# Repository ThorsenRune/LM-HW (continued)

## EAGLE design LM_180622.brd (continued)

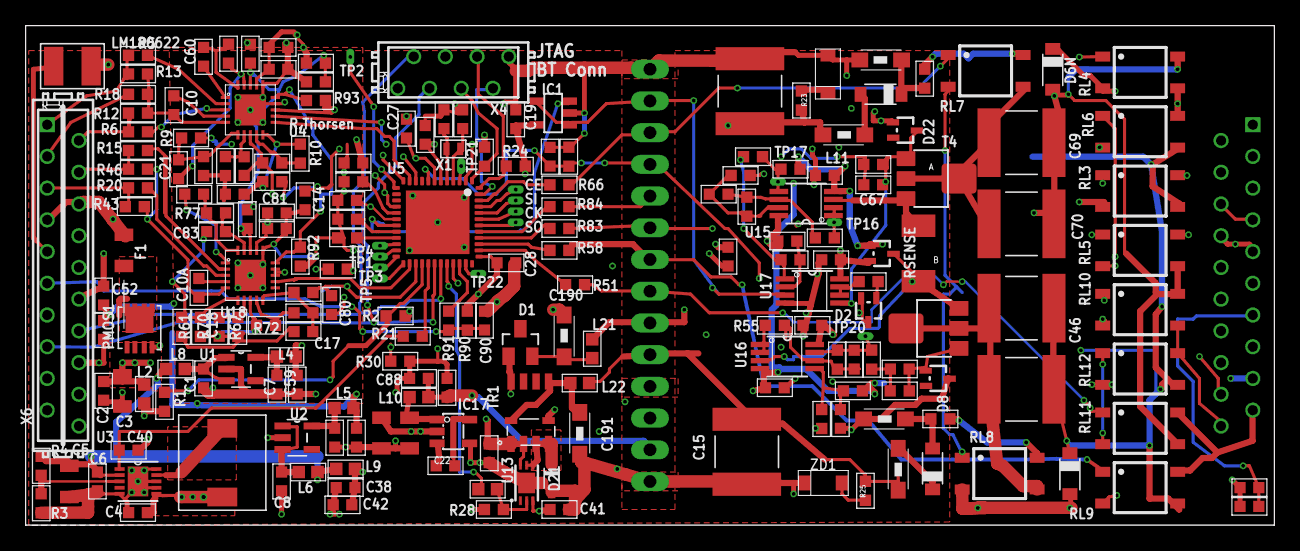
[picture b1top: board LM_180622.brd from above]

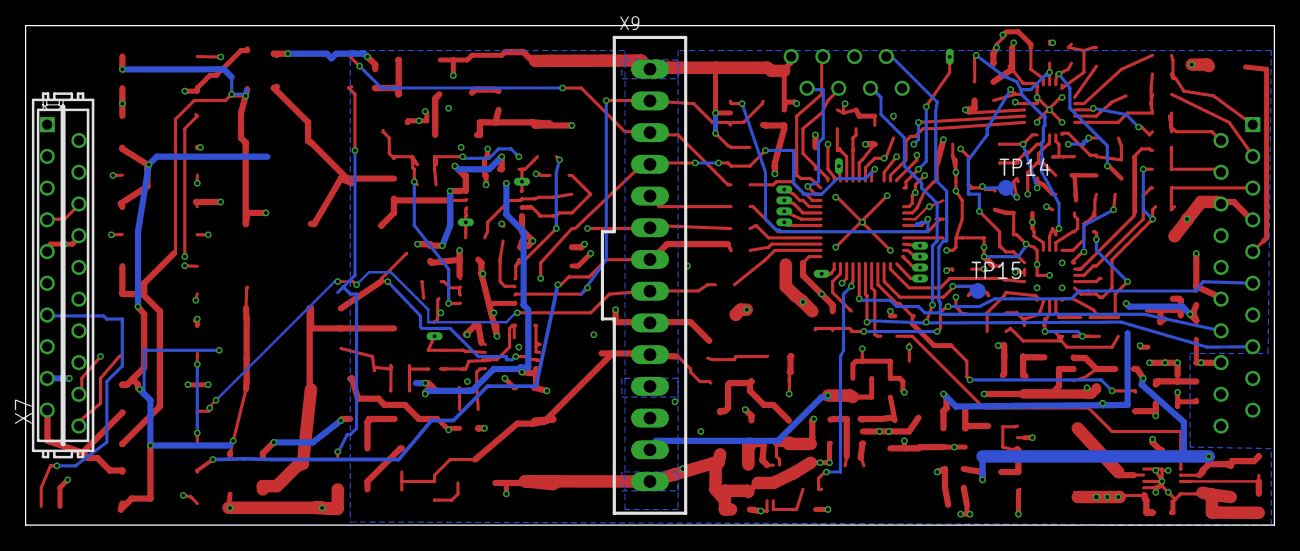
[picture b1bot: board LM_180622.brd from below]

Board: 4 copper layers, 100.0 x 40.0 mm, 216 parts (4 on the bottom side), 149 nets.

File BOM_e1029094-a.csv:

"Reference:,""e1029094-a""";;;;
"Date:,""Fri Jul 20 15:37:21 GMT+200 2018""";;;;
"Generated by:,""Eurocircuits PCBA Visualizer""";;;;

Reference designators;Quantity;MPN;Manufacturer;Description
R30;1;GPR06030R;Generic part;0 Ohms Jumper 0.1W, 1/10W Chip Resistor 0603 (1608 Metric) Moisture Resistant Thick Film
C75, C76;2;C0603C101K5RACTU;Kemet;Capacitor, Ceramic, 100pF 50V 10% X7R
R9, R10, R11, R24, R56, R57, R65, R68, R69, R70, R71, R72;12;GPR0603100K;Generic part;0603, Res 100.0kOhm, 50V, 1.0%, 100mW
C44, C50, C190, C191;4;12062C104KAT2A;AVX;0.1µF ±10% 200V Ceramic Capacitor X7R 1206 (3216 Metric)
C14, C80, C1U15, C1U16, C2U15, C2U16, C19, C20, C23, C24, C28, C31, C40, C41, C42, C45, C48, C49, C53, C67, C82, C86, C88, C90, C144, CU17;26;GPC0603104;Generic part;0603, Cap 100.0nF, 50V, 10.0%, X7R
C55;1;GRM32ER60J107ME20L;Murata;100µF ±20% 6.3V Ceramic Capacitor X5R 1210 (3225 Metric)
R93;1;GPR060310K;Generic part;0603, Res 10.0kOhm, 50V, 1.0%, 100mW
R12, R13, R16, R17, R22, R43, R46, R77, R144, R145;10;CRCW060310M0FKEA;Vishay;10M Ohm ±1% 0.1W, 1/10W Chip Resistor 0603 (1608 Metric) Automotive AEC-Q200 Thick Film
R48, R49;2;GPR060310R;Generic part;0603, Res 10.0Ohm, 50V, 1.0%, 100mW
R7, R8, R21, R61, R67, R89;6;GPR060310K;Generic part;0603, Res 10.0kOhm, 50V, 1.0%, 100mW
C32, C33;2;C0603C100J5GACTU;Kemet;10pF ±5% 50V Ceramic Capacitor C0G, NP0 0603 (1608 Metric)
C1, C2, C4, C6, C7, C8, C9, C16, C29, C30, C38, C52, C54, C58, C59, C81;16;C1608X5R0J106M080AB;TDK;10µF ±20% 6.3V Ceramic Capacitor X5R 0603 (1608 Metric)
R5, R6, R15, R20;4;GPR0603180K;Generic part;0603, Res 180.0kOhm, 50V, 1.0%, 100mW
R28, R40, R42, R62;4;GPR06031M;Generic part;0603, Res 1.0MOhm, 50V, 1.0%, 100mW
R23, R25, R29, R41, R55, R63, R80;7;GPR06031K;Generic part;0603, Res 1.0kOhm, 50V, 1.0%, 100mW
C10, C10A;2;500R14N102JV4T;Johanson Dielectrics Inc.;"1000pF ±5% 50V Ceramic Capacitor C0G, NP0 0603 (1608 Metric) 0.063"" L x 0.032"" W (1.60mm x 0.81mm)"
C22;1;GPC0603105;Generic part;0603, Cap 1uF, 50V, 10.0%, X5R
RSENSE;1;MCPWR10FTEQ2000;Multicomp;RES, THICK FILM, 200R, 1%, 0.75W, 2010
C21, C60, C83, C85;4;C0603C224K3RACTU;Kemet;0.22µF ±10% 25V Ceramic Capacitor X7R 0603 (1608 Metric)
R3;1;GPR0603270K;Generic part;0603, Res 270.0kOhm, 50V, 1.0%, 100mW
R1, R4;2;GPR06032M;Generic part;0603, Res 2.0MOhm, 75V, 1.0%, 100mW
C13, C15, C46, C51, C69, C70;6;C5750X7T2E225K250KE;TDK;2.2µF ±10% 250V Ceramic Capacitor X7T 2220 (5750 Metric)
L2, L3, L4, L5, L6, L8, L9, L10, L21, L22;10;MMZ1608B301CTAH0;TDK;FERRITE BEAD 300 OHM 0603 1LN
C11, C12, C17, C18;4;C0603C333K1RACTU;Kemet;0.033µF ±10% 100V Ceramic Capacitor X7R 0603 (1608 Metric)
R66;1;GPR0603390R;Generic part;0603, Res 390.0Ohm, 50V, 1.0%, 100mW
R2, R90, R91;3;GPR0603390K;Generic part;0603, Res 390.0kOhm, 75V, 1.0%, 100mW
R14, R73;2;GPR06033K3;Generic part;0603, Res 3.3kOhm, 75V, 1.0%, 100mW
C39;1;CGB3B3X5R0J475K055AB;TDK Corporation;"4.7µF ±10% 6.3V Ceramic Capacitor X5R 0603 (1608 Metric) 0.063"" L x 0.032"" W (1.60mm x 0.80mm)"
R19;1;GPR0603470R;Generic part;0603, Res 470.0Ohm, 75V, 1.0%, 100mW
C26, C27, C34;3;GPC0603474;Generic part;0603, Cap 470nF, 50V, 10.0%, X7R
C3, C5;2;GRM219R60J476ME44D;Murata Electronics North America;47µF ±20% 6.3V Ceramic Capacitor X5R 0805 (2012 Metric) GRM Series
L11, L12;2;LQH31MN470K03L;Murata;47µH Unshielded Wirewound Inductor 55mA 10.4 Ohm Max 1206 (3216 Metric)
R18;1;MCWR06X4993FTL;Multicomp;RES, THICK FILM, 499KOHM, 1%, 0.1W, 0603
R64;1;GPR06034K7;Generic part;0603, Res 4.7kOhm, 50V, 1.0%, 100mW
C43, C47;2;GRM21BR60J475KA11L;Murata;4.7µF ±10% 6.3V Ceramic Capacitor X5R 0805 (2012 Metric)
L1;1;B82462G4682M000;EPCOS;6.8µH Shielded Wirewound Inductor 1.65A 50 mOhm Max Nonstandard
R51, R58, R83, R84;4;GPR0603820R;Generic part;0603, Res 820.0Ohm, 50V, 1.0%, 100mW
X1;1;ABS05-32.768KHZ-T;Abracon;32.768kHz ±20ppm Crystal 12.5pF 90 kOhm -40°C ~ 85°C Surface Mount 2-SMD, No Lead
U4, U18;2;AD8232ACPZ-R7;Analog Device;ECG Front End IC Heart Rate Monitoring 20-LFCSP-WQ (4x4)
U15, U16, U17;3;AD8642ARMZ;Analog Device;IC OPAMP JFET 3.5MHZ RRO 8MSOP
U1, U2;2;MIC5255-3.3YM5-TR;Microchip;Linear Voltage Regulator IC Positive Fixed 1 Output 3.3V 150mA SOT-23-5
U5;1;ADUCM360BCPZ128;Analog Device;ARM® Cortex®-M3 ADuCM Microcontroller IC 32-Bit 20 MIPS 128KB (128K x 8) FLASH 48-LFCSP-WQ (7x7)
RL3, RL4, RL5, RL6, RL7, RL8, RL9, RL10, RL11, RL12;10;AQY210S;Panasonic;MOSFET Relay, 350 V, 120 mA, 25 ohm, SPST-NO
TR1;1;ATB322524-0110;TDK;Audio Transformers / Signal Transformers Photoflash Capacitor Charging Transformer
D2, D8, D12, D22;4;BAS40-04W,115;NXP Semiconductors;Diode Array 1 Pair Series Connection Schottky 40V 120mA (DC) Surface Mount SC-70, SOT-323
D1;1;BAV23S,215;Nexperia;Diode Array 1 Pair Series Connection Standard 200V 225mA (DC) Surface Mount TO-236-3, SC-59, SOT-23-3
D6N, D6P, D6P1, D6P2;4;BAV3004W-7-F;Diode Inc;Diode Standard 300V 225mA (DC) Surface Mount SOD-123
F1;1;0805L100WR;Littelfuse;Polymeric PTC Resettable Fuse 6V 1A Ih Surface Mount 0805 (2012 Metric), Concave
ZD1, ZD3;2;KDZLVTFTR150;ROHM Semiconductor;Zener Diode 150V 1W  Surface Mount SOD-123FL
U13;1;LT3484EDCB-1#TRMPBF;Linear Technology/Analog Devices;Photoflash Capacitor Charger PMIC 6-DFN (2x3)
X6;1;9-215464-0;TE Connectivity;"Connector Header Through Hole 20 position 0.100"" (2.54mm)"
X4;1;7-215464-8;TE Connectivity;"Connector Header Through Hole 8 position 0.100"" (2.54mm)"
IC1;1;OPA340NA/3K;Texas Instruments;General Purpose Amplifier 1 Circuit Rail-to-Rail SOT-23-5
PMOS1;1;SIS406DN-T1-GE3;Vishay;N-Channel MOSFET 30V 9A (Ta) 1.5W (Ta) Surface Mount PowerPAK® 1212-8
IC17;1;TPS60400DBVR;Texas Instruments;IC, Unregulated 60mA Charge Pump Voltage Inverter
U3;1;TPS61020DRCRG4;Texas Instrument;DC-DC Switching Boost Step Up Regulator, Adjustable, 900mV-6.5Vin, 1.8V-5.5Vout, 200mAout, SON-10
D21;1;ZHCS400;Diode Inc;Diode Schottky 40V 400mA (DC) Surface Mount SOD-323
T4;1;ZVN4525ZTA;Diode Inc;N-Channel MOSFET 250V 240mA (Ta) 1.2W (Ta) Surface Mount SOT-89-3
T25;1;ZVP4525ZTA;Diodes Incorporated;P-Channel MOSFET 250V 205mA (Ta) 1.2W (Ta) Surface Mount SOT-89-3

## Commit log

2018-12-17 First Version of the LM Hardware
    This hardware is part of a neuroprosthesis aimed at restoring hand function in people with tetraplegia.
    It is a two channel emg amplifier and a two channel functional electrical stimulator controlled by the ADUCM360 microcontroller.
    These are realized using the Eagle version 7 and produced and assembled by EuroCircuits.
    The circuits are tested and functional with some minor bug fixes.
    This part of the LM project has been supported by The Italian Ministry of Health - Ricerca Corrente, the Promobilia Foundation (Sweden) grant no 16066
2019-11-04 PDF versions of the PCB layout
